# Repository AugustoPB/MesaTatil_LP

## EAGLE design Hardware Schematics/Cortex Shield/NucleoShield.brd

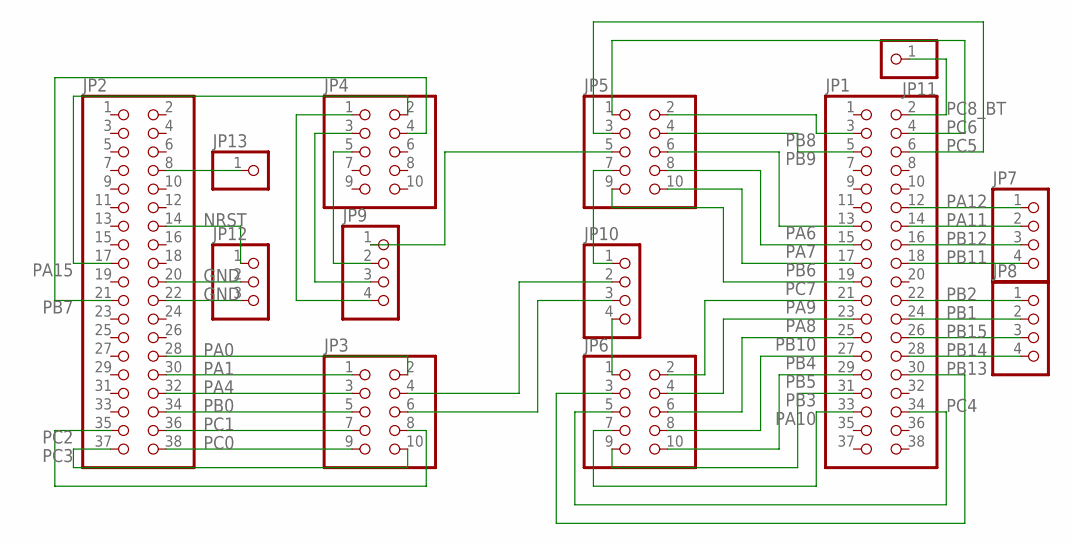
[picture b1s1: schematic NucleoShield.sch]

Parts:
JP1, JP2: PINHD-2X19; 2X19
JP3, JP4, JP5, JP6: PINHD-2X5; 2X05
JP7, JP8, JP9, JP10: PINHD-1X4; 1X04
JP11, JP13: PINHD-1X1; 1X01
JP12: PINHD-1X3; 1X03

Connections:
GND: JP2.20, JP2.22, JP12.2, JP12.3
unnamed: JP3.6, JP10.3
unnamed: JP3.4, JP10.2
unnamed: JP6.1, JP10.4
unnamed: JP5.7, JP10.1
unnamed: JP5.5, JP9.1
unnamed: JP4.5, JP9.2
unnamed: JP4.3, JP9.3
unnamed: JP4.1, JP9.4
unnamed: JP2.8, JP13.1
NRST: JP2.14, JP12.1
PA0: JP2.28, JP3.2
PA1: JP2.30, JP3.1
PA4: JP2.32, JP3.3
PA6: JP1.13, JP5.6
PA7: JP1.15, JP5.8
PA8: JP1.23, JP6.4
PA9: JP1.21, JP6.2
PA10: JP1.33, JP6.7
PA11: JP1.14, JP7.2
PA12: JP1.12, JP7.1
PA15: JP2.17, JP4.2
PB0: JP2.34, JP3.5
PB1: JP1.24, JP8.2
PB2: JP1.22, JP8.1
PB3: JP1.31, JP6.9
PB4: JP1.27, JP6.8
PB5: JP1.29, JP6.10
PB6: JP1.17, JP5.10
PB7: JP2.21, JP4.4
PB8: JP1.3, JP5.2
PB9: JP1.5, JP5.4
PB10: JP1.25, JP6.6
PB11: JP1.18, JP7.4
PB12: JP1.16, JP7.3
PB13: JP1.30, JP6.3
PB14: JP1.28, JP8.4
PB15: JP1.26, JP8.3
PC0: JP2.38, JP3.9
PC1: JP2.36, JP3.7
PC2: JP2.35, JP3.8
PC3: JP2.37, JP3.10
PC4: JP1.34, JP6.5
PC5: JP1.6, JP5.3
PC6: JP1.4, JP5.1
PC7: JP1.19, JP5.9
PC8_BT: JP1.2, JP11.1

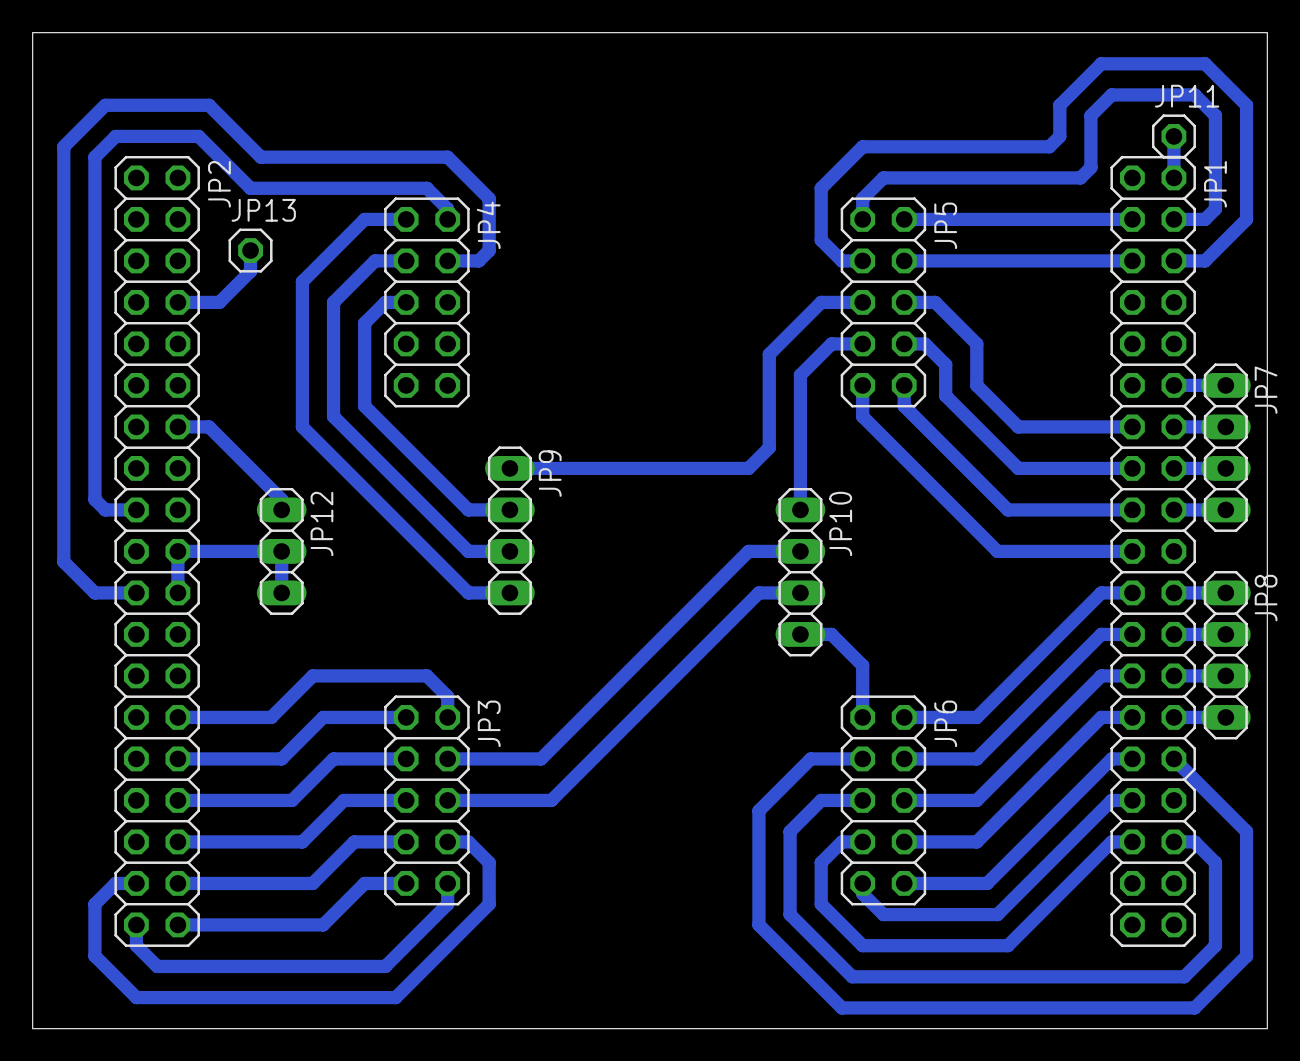
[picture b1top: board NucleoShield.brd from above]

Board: 2 copper layers, 75.6 x 61.0 mm, 13 parts (0 on the bottom side), 47 nets.

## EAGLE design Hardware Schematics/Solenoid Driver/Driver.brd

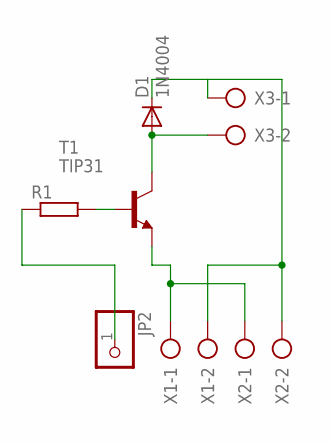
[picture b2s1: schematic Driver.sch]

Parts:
D1: 1N4004; DO41-10
JP2: PINHD-1X1; 1X01
R1: R-EU_0204/2V; 0204V
T1: TIP31; TO220
X1, X2, X3: AK500/2-H

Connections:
GND: T1.3 (E), X1.1, X2.1
unnamed: D1.A, T1.2 (C), X3.2
unnamed: R1.2, T1.1 (B)
unnamed: JP2.1, R1.1
unnamed: D1.C, X1.2, X2.2, X3.1

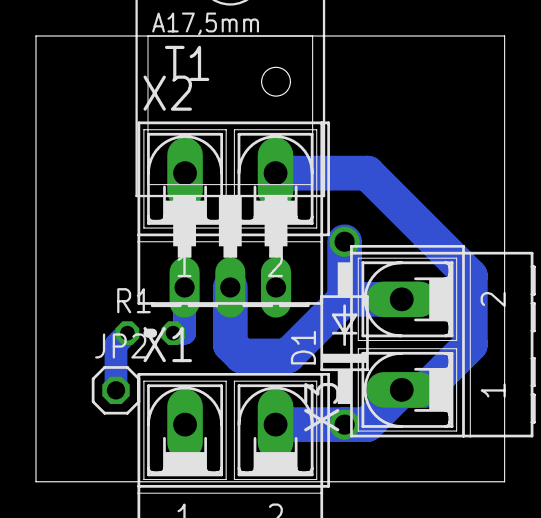
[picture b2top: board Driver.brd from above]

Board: 2 copper layers, 26.0 x 24.8 mm, 7 parts (0 on the bottom side), 5 nets.

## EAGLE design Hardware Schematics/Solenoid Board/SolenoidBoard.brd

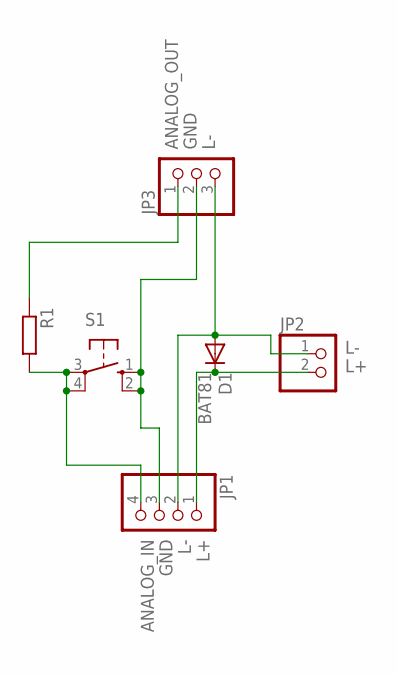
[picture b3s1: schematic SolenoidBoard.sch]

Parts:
D1: BAT81; DO34-7
JP1: PINHD-1X4; 1X04
JP2: PINHD-1X2; 1X02
JP3: PINHD-1X3; 1X03
R1: R-EU_0204/7; 0204/7
S1: 10-XX; B3F-10XX

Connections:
ANALOG_IN: JP1.4, R1.2, S1.3, S1.4 (P1)
ANALOG_OUT: JP3.1, R1.1
GND: JP1.3, JP3.2, S1.1 (S), S1.2 (S1)
L+: D1.C, JP1.1, JP2.2
L-: D1.A, JP1.2, JP2.1, JP3.3

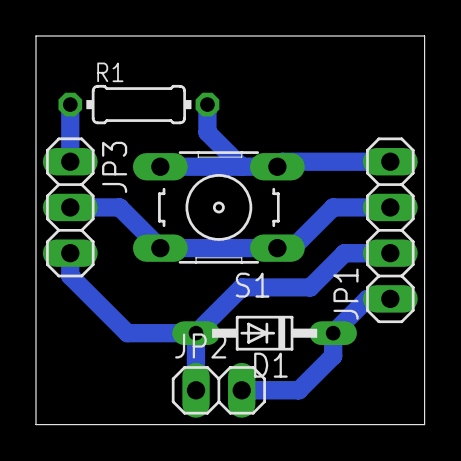
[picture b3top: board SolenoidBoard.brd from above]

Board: 2 copper layers, 21.6 x 21.6 mm, 6 parts (0 on the bottom side), 5 nets.

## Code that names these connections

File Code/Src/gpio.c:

/**
  ******************************************************************************
  * File Name          : gpio.c
  * Description        : This file provides code for the configuration
  *                      of all used GPIO pins.
  ******************************************************************************
  ** This notice applies to any and all portions of this file
  * that are not between comment pairs USER CODE BEGIN and
  * USER CODE END. Other portions of this file, whether 
  * inserted by the user or by software development tools
  * are owned by their respective copyright owners.
  *
  * COPYRIGHT(c) 2017 STMicroelectronics
  *
  * Redistribution and use in source and binary forms, with or without modification,
  * are permitted provided that the following conditions are met:
  *   1. Redistributions of source code must retain the above copyright notice,
  *      this list of conditions and the following disclaimer.
  *   2. Redistributions in binary form must reproduce the above copyright notice,
  *      this list of conditions and the following disclaimer in the documentation
  *      and/or other materials provided with the distribution.
  *   3. Neither the name of STMicroelectronics nor the names of its contributors
  *      may be used to endorse or promote products derived from this software
  *      without specific prior written permission.
  *
  * THIS SOFTWARE IS PROVIDED BY THE COPYRIGHT HOLDERS AND CONTRIBUTORS "AS IS"
  * AND ANY EXPRESS OR IMPLIED WARRANTIES, INCLUDING, BUT NOT LIMITED TO, THE
  * IMPLIED WARRANTIES OF MERCHANTABILITY AND FITNESS FOR A PARTICULAR PURPOSE ARE
  * DISCLAIMED. IN NO EVENT SHALL THE COPYRIGHT HOLDER OR CONTRIBUTORS BE LIABLE
  * FOR ANY DIRECT, INDIRECT, INCIDENTAL, SPECIAL, EXEMPLARY, OR CONSEQUENTIAL
  * DAMAGES (INCLUDING, BUT NOT LIMITED TO, PROCUREMENT OF SUBSTITUTE GOODS OR
  * SERVICES; LOSS OF USE, DATA, OR PROFITS; OR BUSINESS INTERRUPTION) HOWEVER
  * CAUSED AND ON ANY THEORY OF LIABILITY, WHETHER IN CONTRACT, STRICT LIABILITY,
  * OR TORT (INCLUDING NEGLIGENCE OR OTHERWISE) ARISING IN ANY WAY OUT OF THE USE
  * OF THIS SOFTWARE, EVEN IF ADVISED OF THE POSSIBILITY OF SUCH DAMAGE.
  *
  ******************************************************************************
  */

/* Includes ------------------------------------------------------------------*/
#include "gpio.h"
/* USER CODE BEGIN 0 */

/* USER CODE END 0 */

/*----------------------------------------------------------------------------*/
/* Configure GPIO                                                             */
/*----------------------------------------------------------------------------*/
/* USER CODE BEGIN 1 */

/* USER CODE END 1 */

/** Configure pins as 
        * Analog 
        * Input 
        * Output
        * EVENT_OUT
        * EXTI
*/
void MX_GPIO_Init(void)
{

  GPIO_InitTypeDef GPIO_InitStruct;

  /* GPIO Ports Clock Enable */
  __HAL_RCC_GPIOC_CLK_ENABLE();
  __HAL_RCC_GPIOF_CLK_ENABLE();
  __HAL_RCC_GPIOA_CLK_ENABLE();
  __HAL_RCC_GPIOB_CLK_ENABLE();

  /*Configure GPIO pin Output Level */
  HAL_GPIO_WritePin(GPIOC, GPIO_PIN_0|GPIO_PIN_1|GPIO_PIN_2|GPIO_PIN_3 
                          |GPIO_PIN_4|GPIO_PIN_5|GPIO_PIN_6|GPIO_PIN_7, GPIO_PIN_RESET);

  /*Configure GPIO pin Output Level */
  HAL_GPIO_WritePin(GPIOA, GPIO_PIN_0|GPIO_PIN_1|GPIO_PIN_4|LD2_Pin 
                          |GPIO_PIN_6|GPIO_PIN_7|GPIO_PIN_8|GPIO_PIN_9 
                          |GPIO_PIN_10|GPIO_PIN_11|GPIO_PIN_12|GPIO_PIN_15, GPIO_PIN_RESET);

  /*Configure GPIO pin Output Level */
  HAL_GPIO_WritePin(GPIOB, GPIO_PIN_0|GPIO_PIN_1|GPIO_PIN_2|GPIO_PIN_10 
                          |GPIO_PIN_11|GPIO_PIN_12|GPIO_PIN_13|GPIO_PIN_14 
                          |GPIO_PIN_15|GPIO_PIN_3|GPIO_PIN_4|GPIO_PIN_5 
                          |GPIO_PIN_6|GPIO_PIN_7|GPIO_PIN_8|GPIO_PIN_9, GPIO_PIN_RESET);

  /*Configure GPIO pin : PtPin */
  GPIO_InitStruct.Pin = B1_Pin;
  GPIO_InitStruct.Mode = GPIO_MODE_IT_FALLING;
  GPIO_InitStruct.Pull = GPIO_NOPULL;
  HAL_GPIO_Init(B1_GPIO_Port, &GPIO_InitStruct);

  /*Configure GPIO pins : PC0 PC1 PC2 PC3 
                           PC4 PC5 PC6 PC7 */
  GPIO_InitStruct.Pin = GPIO_PIN_0|GPIO_PIN_1|GPIO_PIN_2|GPIO_PIN_3 
                          |GPIO_PIN_4|GPIO_PIN_5|GPIO_PIN_6|GPIO_PIN_7;
  GPIO_InitStruct.Mode = GPIO_MODE_OUTPUT_PP;
  GPIO_InitStruct.Pull = GPIO_NOPULL;
  GPIO_InitStruct.Speed = GPIO_SPEED_FREQ_LOW;
  HAL_GPIO_Init(GPIOC, &GPIO_InitStruct);

  /*Configure GPIO pins : PA0 PA1 PA4 PAPin 
                           PA6 PA7 PA8 PA9 
                           PA10 PA11 PA12 PA15 */
  GPIO_InitStruct.Pin = GPIO_PIN_0|GPIO_PIN_1|GPIO_PIN_4|LD2_Pin 
                          |GPIO_PIN_6|GPIO_PIN_7|GPIO_PIN_8|GPIO_PIN_9 
                          |GPIO_PIN_10|GPIO_PIN_11|GPIO_PIN_12|GPIO_PIN_15;
  GPIO_InitStruct.Mode = GPIO_MODE_OUTPUT_PP;
  GPIO_InitStruct.Pull = GPIO_NOPULL;
  GPIO_InitStruct.Speed = GPIO_SPEED_FREQ_LOW;
  HAL_GPIO_Init(GPIOA, &GPIO_InitStruct);

  /*Configure GPIO pins : PB0 PB1 PB2 PB10 
                           PB11 PB12 PB13 PB14 
                           PB15 PB3 PB4 PB5 
                           PB6 PB7 PB8 PB9 */
  GPIO_InitStruct.Pin = GPIO_PIN_0|GPIO_PIN_1|GPIO_PIN_2|GPIO_PIN_10 
                          |GPIO_PIN_11|GPIO_PIN_12|GPIO_PIN_13|GPIO_PIN_14 
                          |GPIO_PIN_15|GPIO_PIN_3|GPIO_PIN_4|GPIO_PIN_5 
                          |GPIO_PIN_6|GPIO_PIN_7|GPIO_PIN_8|GPIO_PIN_9;
  GPIO_InitStruct.Mode = GPIO_MODE_OUTPUT_PP;
  GPIO_InitStruct.Pull = GPIO_NOPULL;
  GPIO_InitStruct.Speed = GPIO_SPEED_FREQ_LOW;
  HAL_GPIO_Init(GPIOB, &GPIO_InitStruct);

  /*Configure GPIO pin : PC8 */
  GPIO_InitStruct.Pin = GPIO_PIN_8;
  GPIO_InitStruct.Mode = GPIO_MODE_INPUT;
  GPIO_InitStruct.Pull = GPIO_PULLUP;
  HAL_GPIO_Init(GPIOC, &GPIO_InitStruct);

}

/* USER CODE BEGIN 2 */

/* USER CODE END 2 */

/**
  * @}
  */

/**
  * @}
  */

/************************ (C) COPYRIGHT STMicroelectronics *****END OF FILE****/

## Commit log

2017-06-16 Initial Concept
2017-06-23 New Solenoid Driver Design
2017-07-04 Updating Repository
2017-07-04 add wave forms library
2017-07-11 Update Code and add Nucleo shield
2017-07-11 Fix Commit
